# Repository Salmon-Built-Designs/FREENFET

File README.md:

Freetronics FreeNFET Addressable N-MOSFET Module
================================================
Copyright 2016 Freetronics Pty Ltd  
Freetronics site:  www.freetronics.com  
Freetronics email: info@freetronics.com  

This is a FET with a brain! Includes an NTD5867NL N-channel MOSFET and
a WS2811 addressable LED driver. That means you can connect the module
and address it just as if it was a NeoPixel or other WS28xx RGB LED, 
except that instead of controlling an LED, you're controlling a high-power
MOSFET.

This smart module can be daisy-chained, so you can connect a number of
these together in a string and drive each of them individually from your
microcontroller.

Compatible with various Arduino libraries for the WS2811, including
the FastLED library and the NeoPixel library. Simply control the "red"
channel to control the FET.

Features:

 * Switch up to 60V / 18A DC.
 * Requires just 1 data connection.
 * PWM control of the FET.
 * Input and output headers on opposite sides of the board for easy
   daisy-chaining.

More information is available at:

  http://www.freetronics.com.au/freenfet

INSTALLATION
------------
The design is saved as an EAGLE project. EAGLE PCB design software is
available from www.cadsoftusa.com free for non-commercial use. To use
this project download it and place the directory containing these files
into the "eagle" directory on your computer.

DISTRIBUTION
------------
The specific terms of distribution of this project are governed by the
license referenced below.

LICENSE
-------
Licensed under the TAPR Open Hardware License (www.tapr.org/OHL).
The "license" folder within this repository also contains a copy of
this license in plain text format.

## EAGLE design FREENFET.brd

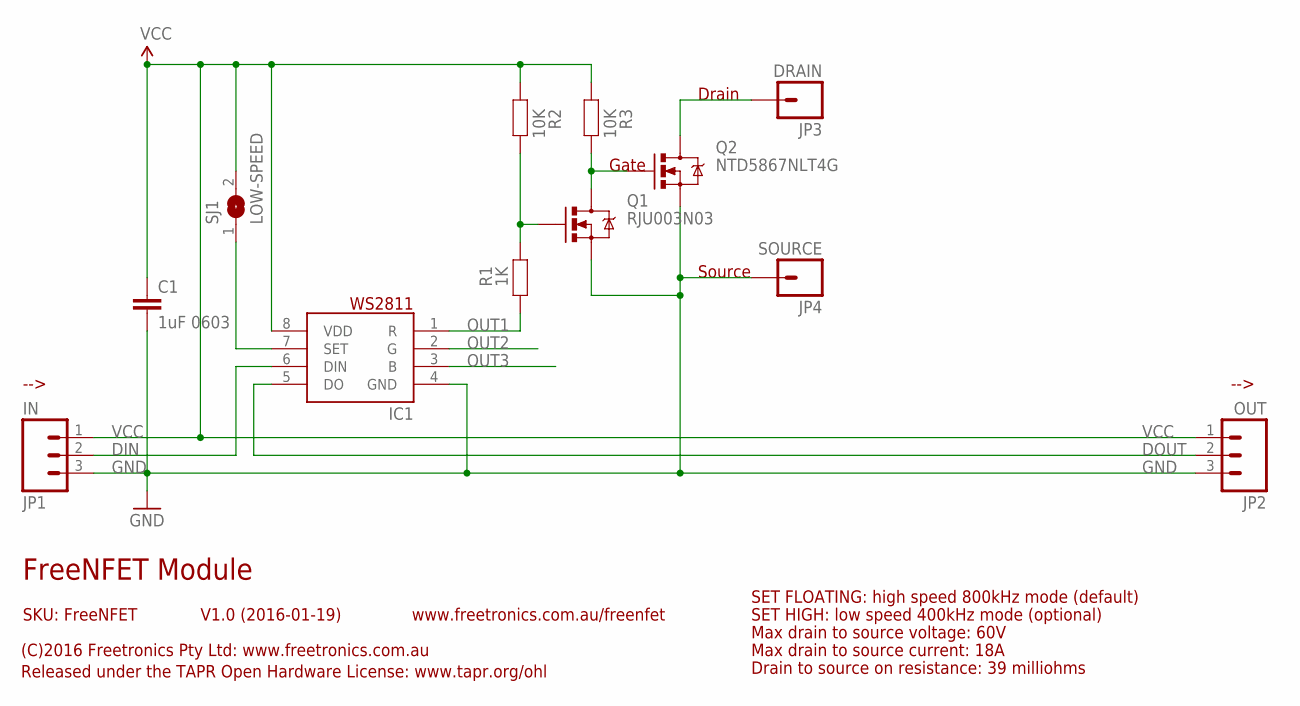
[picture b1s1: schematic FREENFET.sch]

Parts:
C1: 1uF 0603; 0603
IC1: WS2811-SOP8; SO08-SKINNYPADS
JP1: IN; 1X03
JP2: OUT; 1X03
JP3: DRAIN; 1X01LARGE
JP4: SOURCE; 1X01LARGE
Q1: RJU003N03; SOT32-3
Q2: NTD5867NLT4G; DPACK
R1: 1K; 0603
R2, R3: 10K; 0603
SJ1: LOW-SPEED; SJ

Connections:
D: JP3.1, Q2.2 (D)
DIN: IC1.6 (DIN), JP1.2
DOUT: IC1.5 (DO), JP2.2
GND: C1.2, IC1.4 (GND), JP1.3, JP2.3, JP4.1, Q1.2 (S), Q2.3 (S)
unnamed: IC1.7 (SET), SJ1.1
unnamed: Q1.1 (G), R1.1, R2.1
unnamed: Q1.3 (D), Q2.1 (G), R3.1
OUT1: IC1.1 (R), R1.2
OUT2: IC1.2 (G)
OUT3: IC1.3 (B)
VCC: C1.1, IC1.8 (VDD), JP1.1, JP2.1, R2.2, R3.2, SJ1.2

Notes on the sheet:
FreeNFET Module
V1.0 (2016-01-19)
SKU: FreeNFET
(C)2016 Freetronics Pty Ltd: www.freetronics.com.au
Released under the TAPR Open Hardware License: www.tapr.org/ohl
www.freetronics.com.au/freenfet
-->
SET HIGH: low speed 400kHz mode (optional)
Max drain to source current: 18A
Drain
Gate
Source
Max drain to source voltage: 60V
Drain to source on resistance: 39 milliohms
SET FLOATING: high speed 800kHz mode (default)

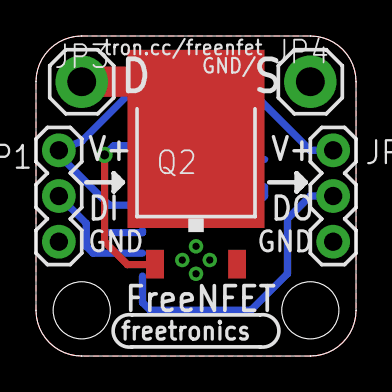
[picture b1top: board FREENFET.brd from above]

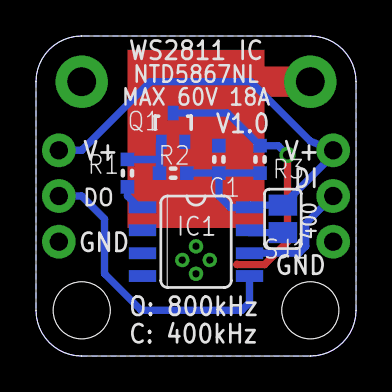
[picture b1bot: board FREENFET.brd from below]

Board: 2 copper layers, 17.8 x 17.8 mm, 12 parts (7 on the bottom side), 9 nets.

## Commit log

2016-03-15 Initial import of project for v1.0 release
2016-03-15 Updated license file
2016-03-30 Clarified schematic and silkscreen
2019-04-23 Designator improvement
